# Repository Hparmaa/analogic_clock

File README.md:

# Cronômetro Digital TTL/CMOS

Projeto de um cronômetro digital utilizando circuitos TTL/CMOS, displays de 7 segmentos e alimentação diretamente da rede elétrica da CEMIG.

## Licença

Este projeto é licenciado sob a CERN-OHL-S v2.

## Recursos do projeto

- Contagem de minutos e segundos
- Clock derivado da rede elétrica de 60 Hz
- Displays de 7 segmentos
- Circuitos TTL/CMOS
- Projeto desenvolvido no KiCad
## 
1.	OBJETIVO
   
Projetar e implementar um cronômetro digital capaz de contar os segundos e minutos. O dispositivo deverá ser alimentado exclusivamente a partir da rede elétrica da CEMIG. O cronômetro deverá possuir dois botões, sendo um para iniciar e parar a contagem do tempo (start/stop) e outro para zerar a contagem (reset). Os segundos e minutos serão mostrados em quatro displays de sete segmentos, sendo dois para os segundos (dezena e unidade) e dois para os minutos (dezena e unidade).

## 
2.	DESENVOLVIMENTO
   
O sistema foi dividido em três subsistemas distintos e interligados, sendo eles : 

•	Circuito para a alimentação e geração de clock;

•	Circuito lógico de contagem;

•	Circuito para mostrar a contagem.

A seguir será apresentado o desenvolvimento de cada um destes subsistemas. Todos os diagramas foram montados no software KiCAD.

2.1.	Circuito para a Alimentação e Geração de Clock

De acordo com o meu objetivo ao realizar esse projeto, o cronômetro digital deverá ser alimentado exclusivamente a partir da rede elétrica da CEMIG, a qual possui uma tensão senoidal com tensão eficaz de 127 V e 60 Hz. Considerando que os circuitos integrados a serem utilizados serão do tipo TTL ou CMOS, alimentados em 5 V, tensão contínua, será necessário converter a tensão alternada de 127 VAC em 5 VCC. Por isso, utilizei um retificador de onda completa com um regulador linear de tensão.
O circuito lógico de contagem requer um sinal de clock com frequência fixa e níveis adequados de tensão para uma contagem precisa. Sei que a rede elétrica da CEMIG provê uma senoide com frequência de 60 Hz. Portanto, optei por condicionar a senoide fornecida pela CEMIG para gerar um clock com os mesmos 60 Hz, o qual será posteriormente utilizado no circuito lógico de contagem.
A Figura 1 apresenta o circuito desenvolvido para a alimentação e geração de clock.

Figura 1 – Circuito para alimentação e geração de clock.

Para um adequado funcionamento do circuito de geração do clock e circuito de alimentação, será utilizado um transformador de três enrolamentos de 127 V/7,5 V/7,5 V. Entretanto, considerando que não foi encontrado este tipo de transformador no comércio local, na montagem, foram utilizados dois transformadores distintos, um de 1 A e outro de 0,5 A.

Os componentes para o circuito de geração de clock foram escolhidos conforme explicado a seguir:

Tensão de saída do enrolamento do transformador de 7,5 V, 500 mA.

D9: diodo zenner. Foi escolhido um diodo zenner de 5,1 Volts quando é reversamente polarizado. Quando diretamente polarizado sua tensão é de 1,5 V. Vou considerar que ali vai passar metade da corrente máxima(200mA) suportada por ele, ou seja, projetei o resistor R35 para 100mA.

R35: utilizado para limitar a corrente do diodo zenner. Considerando a corrente máxima no zenner em função de sua potência máxima (de acordo com o datasheet) e a tensão de pico da senoide na saída do transformador (pior caso da tensão), quando o zenner estiver diretamente polarizado, tem-se:
R35=(10,6-1,5)/0,1
R35=91 Ω

Para este valor de resistência, haverá uma potência dissipada de:
P=(7,5-1,5)*0,1
P=0,6 W
Comercialmente foi escolhido um resistor de 100 Ω e 1 W.

D12: diodo de germânio. Escolhi um diodo de germânio pois, quando diretamente polarizado, possui uma tensão direta de  0,3 V, e este valor está dentro da faixa de valores permitidos pelo Schimdt trigger. A corrente máxima de diodos comuns como o 1N34A tem como corrente máxima 50 mA, valor que eu utilizei para calcular o valor da resistência R36.

R36: utilizado para limitar a corrente no diodo de germânio. 

R36=(1,5-0,3)/0,05
R36=24 Ω
Para este valor de resistência, haverá uma potência dissipada de:
P=(1,5-0,3)*0,05
P=0,06 W
Comercialmente foi escolhido um resistor de 24 Ω e 1/4 W.

CI U44: Schimdt trigger. Utilizado para o condicionamento final da senoide ceifada. Escolhi um Schimdt trigger alimentado com 5 Volts e cuja tensão de entrada varie de -0,5 até Vcc + 0,5. Segundo o datasheet, ele funciona, para 4,5 V de alimentação, com uma mudança para nível logico alto de 3,15 V e com a mudança para nível lógico baixo de 2,3 V. Escolhi o 74HC14A

Dessa forma, após o condicionamento da senoide entregue pela CEMIG, teremos um CLK1 de 60 Hz, com as tensões adequadas para os níveis lógicos 1 e 0, com relação ao referencial GND.

Os componentes para o circuito de alimentação foram escolhidos conforme explicado a seguir:

Tensão de saída do enrolamento do transformador de 7,5 V (valor eficaz), corrente de 1 A.

D7,D8, D10 e D11: Ponte retificadora em onda completa. Foram definidos os diodos 1N4007, amplamente utilizados neste tipo de circuito. Estes diodos suportam, facilmente, a corrente máxima do regulador de tensão. Foi considerada uma corrente de carga máxima de 1 A.
  
U43: Regulador linear de tensão. Foi escolhido o LM7805, o qual possui uma corrente máxima de 1 A e tensão de saída de 5 V.
  
C4: capacitor de saída da ponte retificadora completa. Utilizado para limitar a tensão de ripple da fonte. O LM7805 requer uma tensão mínima de 7 V para que eu tenha 5V na saída, logo, o meu ripple tem que ser de (10,6-7) = 3,6 V. Assim, minha capacitância é de: 

  C=I/(Vripple*f)
  
  C=1/(3,6*120)

  C=2,31 mF

Esse capacitor deverá ser eletrolítico e sua tensão máxima será de (10,6-1,4) =  9,2 V. 
Considerando valores comerciais, foi escolhido um capacitor eletrolítico de 2200 microF, 25 V.

C5: capacitor de disco de cerâmica de 0,22 microF, indicado no datasheet do LM7805.
  C6: capacitor de disco de cerâmica de 0,1 microF, indicado no datasheet do LM7805.

Desta forma, na saída do circuito de alimentação teremos uma tensão contínua de 5 V, com relação ao referencial GND.

Optou-se por implementar o circuito para alimentação e geração do clock em uma placa de circuito impressa. A Figura 2 apresenta o diagrama de roteamento da placa desenvolvida, vista pelo lado dos componentes. Ressalta-se que as ilhas dos conectores de entrada (transformador) e saída (GND, + 5 V e CLK1) não condizem com a realidade. Da mesma forma, a largura das trilhas também não condiz com a realidade implementada. A numeração dos componentes não possui relação direta com a numeração apresentada na Figura 1.

Figura 2: Diagrama de roteamento da placa do circuito para alimentação e geração do clock.

2.2.	Circuito Lógico de Contagem
O circuito lógico de contagem é o circuito responsável pela lógica de contagem do cronômetro. Esse circuito receberá o sinal de CLK1 e a tensão de 5 VDC da placa de alimentação e geração clock.
A Figura 3 apresenta o circuito lógico de contagem.

Figura 3: Diagrama do circuito lógico de contagem.

Conforme dito, o circuito lógico de contagem recebe o sinal de clock CLK1, que possui frequência de 60 Hz. Considerando que a menor medida de tempo a ser contada são os segundos, será necessário dividir essa frequência por 60. Para isso, foi projetado um contador síncrono, módulo-60, que conte de 0 a 59, ou seja, ao chegar em 60, ou 111100 em binário, ele resete. Dessa forma, na saída desse divisor teremos um clock de 1 Hz. Esse circuito possui, ainda, as chaves de start/stop, sendo ela uma chave de duas posições e a chave de reset, do tipo push bottom.

A saída do divisor módulo-60 (com frequencia de 1 Hz) alimentará um circuito com contadores de década utilizado para a contagem dos segundos e minutos.

Os componentes para o circuito de lógica de contagem foram escolhidos conforme explicado a seguir:

  •	CIs U27, U28 e U28. Foram utilizados seis flip-flops do tipo JK, configurados como flip-flop tipo T, para a implementação do divisor módulo-60. Foi escolhido o CI 4027.

  •	CI U38: para a implementação do divisor módulo-60 foi necessário utilizar uma AND de quatro entradas, utilizada para zerar os flip-flops tipo T quando a contagem chega em 111100. Foi escolhido o CI 7421.
  
  •	SW4: chave de duas posições, on/off. Utilizada para implementar o sistema de start/stop do cronômetro. Essa chave habilita ou desabilita a saída do clock do divisor módulo-60 para o circuito contador dos segundos e minutos.
  
  •	CI U35A: porta AND de duas entradas, utilizado para implementar a lógica de habilitação/desabilitação do sinal de clock de saída do divisor módulo-60.
  
  •	CIs U29, U32, U39 e U40: Decidi utilizar contadores de década (contagem BCD) para a a contagem dos segundos e minutos de forma assíncrona. 
     
Os CIs U29 e U32 são utilizados para a contagem dos segundos (contagem de 0 a 59), utilizando o sinal de clock de saída do divisor de módulo-60. O CI U29 é utilizado para a contagem das unidades de segundo e o CI U32 para a contagem das dezenas de segundos, utilizando a saída do CI U29 como sinal de clock, após a divisão por 10. Os dois contadores são zerados quando U32 atinge o número 6, 0110 em binário, o que equivale a chegar ao número 60 nos dois contadores (conta de 0 a 59 segundos).
 
  Os CIs U39 e U40 são utilizados para a contagem dos minutos (contagem de 0 a 59), utilizando como clock a saída do CI U32. Os dois contadores são zerados quando U40 atinge o número 6 (0110 em binário), o que equivale a chegar ao número 60 nos dois contadores (conta de 0 a 59 minutos).

  •	SW3: chave NA do tipo push bottom. Utilizada para implementar o sistema de reset do cronômetro. Ao ser pressionada os contadores BCD (CIs U29, U32, U39 e U40, responsáveis por contar os segundos e minutos) são resetados.

  •	CI U36: porta OR de duas entradas. Utilizado para implementar a lógica do botão de reset.
  
  •	R33 e R34: resistores utilizados em série com as chaves SW3 e SW4 para a implementação das lógicas de start/stop e reset. Foram utilizados resistores de 10 kΩ, valor suficiente para limitar a corrente quando as chaves forem acionadas sem prejudicar o valor dos níveis digitais aplicados às entradas das portas lógicas.
  
  •	J1, J2, J3 e J4: conectores de 4 pinos para disponibilizar os quatro bits da saída dos contadores de década (contagem BCD).

A saída do circuito lógico de contagem são quatro conjuntos de quatro bits (contagem BCD), responsáveis pela contagem das unidades de segundos, dezenas de segundos, unidades de minutos e dezenas de minutos. Esses sinais são disponibilizados nos conectores J1 a J4.

  Optou-se por implementar o circuito lógico de contagem em um protoboard, devido a complexidade deste circuito.

2.3.	Circuito para Mostrar a Contagem

O circuito para mostrar a contagem é o circuito responsável por mostrar, ao usuário, a contagem do cronômetro.  Esse circuito receberá a tensão de 5 VDC da placa de alimentação e geração clock e os quatro conjuntos de quatro bits (contagem BCD) do circuito lógico de contagem.

  O valor da contagem dos segundos e minutos será apresentado em displays de sete segmentos, totalizando quatro display, dois para os segundos (unidades e dezenas) e dois para os minutos (unidades e dezenas). Para a implementação foram utilizados conversores BCD para 7 segmentos.
  
A Figura 4 apresenta o diagrama do circuito para mostrar o valor da contagem.

Figura 4: Diagrama do circuito para mostrar a contagem.

Os componentes do circuito para mostrar a contagem foram escolhidos conforme explicado a seguir:

J5, J6, J7 e J8: conectores de 4 pinos para receber os quatros bits da contagem da unidade dos segundos, dezena dos segundos, unidade dos minutos e dezena dos minutos.
  
U30, U33, U41 e U45: conversores de BCD para 7 segmentos. Foram utilizados o CI 4511.
  
R37 a R64 (28 resistores): resistores utilizados para limitar a corrente fornecida pelos conversores de BCD para 7 segmentos, considerando a corrente necessária para o adequado funcionamento dos displays de 7 segmentos.
  
Para os leds dos displays acenderem em intensidade média, o datasheet e indica que é necessário 10 mA, logo, usarei 12mA. O datasheet informa, também, que a tensão direta dos leds é de 2 V. Considerando a saída em 5 V do conversor BCD para 7 segmentos, temos:

R=(5-2)/0,012

R=250 Ω

Para esse valor de resistência, a potência será de:

P=3*0,012

P=0,036 W

Será utilizado o valor comercial de R = 250 Ω e ¼ W.

U31, U34, U37 e U47: displays de 7 segmentos de alto brilho, na cor vermelha. Foram utilizados displays de catodo comum, tendo sido utilizado o modelo 5161AS, disponível no comércio local.

SW5: chave NA do tipo push bottom utilizada para implementar o teste dos displays.

R65: resistor utilizado em série com a chave SW5 para a implementação das lógicas teste dos displays. Foi utilizado um resistor de 1,0 kΩ., valor suficiente para limitar a corrente quando a chave for acionada sem prejudicar o valor dos níveis digitais aplicados às entradas dos conversores BCD para 7 segmentos.

Optou-se por implementar o circuito para mostrar a contagem em uma placa de circuito impressa. A Figura 5 apresenta o diagrama de roteamento da placa desenvolvida, vista pelo lado dos componentes. Ressalta-se que a largura das trilhas não condiz com a realidade implementada. A numeração dos componentes não possui relação direta com a numeração apresentada na Figura 4.

Figura 5 - Diagrama de roteamento da placa do circuito para mostrar a contagem.

## 
3.	CONCLUSÃO

Neste trabalho foi projetado um cronômetro digital capaz de marcar os segundos e minutos a partir do comando do usuário, dados por chaves. O cronômetro digital é alimentado a partir da rede elétrica da CEMIG, sendo que o sinal de clock é gerado a partir do condicionamento da senoide de tensão da alimentação, o que garante estabilidade na contagem.

O valor da contagem é apresentado em quatro displays de sete segmentos na cor vermelha e alto brilho.

O projeto foi segmentado em três subsistemas, o primeiro dedicado à geração de tensão contínua de 5 V, com relação ao GND, a ser utilizada em todo o projeto e à geração do sinal de clock de 60 Hz a partir da própria senoide da tensão de alimentação. O segundo dedicado à contagem propriamente dita do cronômetro. O terceiro dedicado a apresentar o valor da contagem ao usuário.

O primeiro e terceiro subsistemas foram implementados em placas de circuito impresso. O segundo sistema foi implementado em um protoboard.

Infelizmente, devido a complexidade do projeto pretendido e à falta de tempos disponível, não foi possível concluir satisfatoriamente o segundo sistema, não sendo possível, portanto, testar todo o sistema proposto. Entende-se, entretanto, que após a finalização do segundo sistema o projeto proposto funcionará a contento.

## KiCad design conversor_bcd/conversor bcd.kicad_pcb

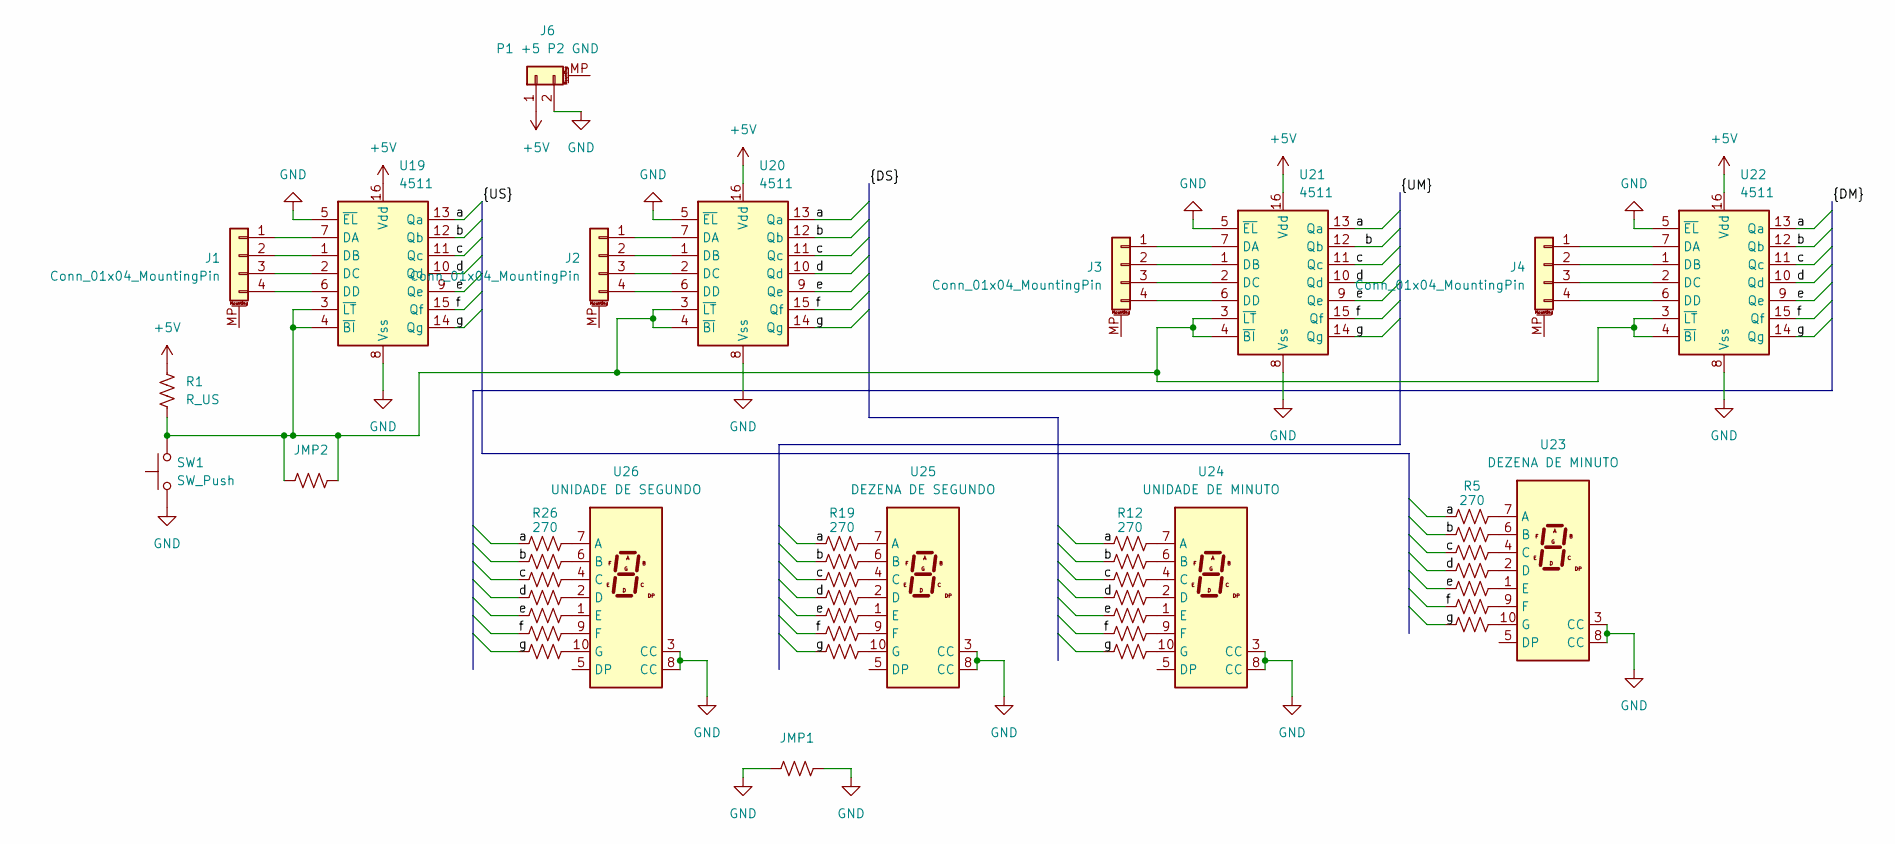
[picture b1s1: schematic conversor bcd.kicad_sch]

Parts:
J1, J2, J3, J4: Conn_01x04_MountingPin; FanPinHeader_1x04_P2.54mm_Vertical
J6: P1 +5 P2 GND; FanPinHeader_1x03_P2.54mm_Vertical
JMP1, JMP2: 1; R_Axial_DIN0411_L9.9mm_D3.6mm_P7.62mm_Vertical
R1: R_US; R_Axial_DIN0411_L9.9mm_D3.6mm_P15.24mm_Horizontal
R5, R6, R7, R8, R9, R10, R11, R12, R13, R14, R15, R16, R17, R18, R19, R20, R21, R22, R23, R24, R25, R26, R27, R28, R29, R30, R31, R32: 270; R_Axial_DIN0411_L9.9mm_D3.6mm_P15.24mm_Horizontal
SW1: SW_Push; SW_PUSH_1P1T_6x3.5mm_H4.3_APEM_MJTP1243
U19, U20, U21, U22: 4511; DIP-16_W7.62mm_Socket
U23: DEZENA DE MINUTO; D1X8K
U24: UNIDADE DE MINUTO; D1X8K
U25: DEZENA DE SEGUNDO; D1X8K
U26: UNIDADE DE SEGUNDO; D1X8K

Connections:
+5V: J6.1, R1.1, U19.16 (Vdd), U20.16 (Vdd), U21.16 (Vdd), U22.16 (Vdd)
/a: R5.1, R12.1, R19.1, R26.1, U19.13 (Qa), U20.13 (Qa), U21.13 (Qa), U22.13 (Qa)
/b: R6.1, R13.1, R20.1, R27.1, U19.12 (Qb), U20.12 (Qb), U21.12 (Qb), U22.12 (Qb)
/c: R7.1, R14.1, R21.1, R28.1, U19.11 (Qc), U20.11 (Qc), U21.11 (Qc), U22.11 (Qc)
/d: R8.1, R15.1, R22.1, R29.1, U19.10 (Qd), U20.10 (Qd), U21.10 (Qd), U22.10 (Qd)
/e: R9.1, R16.1, R23.1, R30.1, U19.9 (Qe), U20.9 (Qe), U21.9 (Qe), U22.9 (Qe)
/f: R10.1, R17.1, R24.1, R31.1, U19.15 (Qf), U20.15 (Qf), U21.15 (Qf), U22.15 (Qf)
/g: R11.1, R18.1, R25.1, R32.1, U19.14 (Qg), U20.14 (Qg), U21.14 (Qg), U22.14 (Qg)
GND: J6.2, JMP1.1, JMP1.2, SW1.1, U19.5 (~EL), U19.8 (Vss), U20.5 (~EL), U20.8 (Vss), U21.5 (~EL), U21.8 (Vss), U22.5 (~EL), U22.8 (Vss), U23.3 (CC), U23.8 (CC), U24.3 (CC), U24.8 (CC), U25.3 (CC), U25.8 (CC), U26.3 (CC), U26.8 (CC)
unnamed: J1.1, U19.7 (DA)
unnamed: J1.2, U19.1 (DB)
unnamed: J1.3, U19.2 (DC)
unnamed: J1.4, U19.6 (DD)
unnamed: J2.1, U20.7 (DA)
unnamed: J2.2, U20.1 (DB)
unnamed: J2.3, U20.2 (DC)
unnamed: J2.4, U20.6 (DD)
unnamed: J3.1, U21.7 (DA)
unnamed: J3.2, U21.1 (DB)
unnamed: J3.3, U21.2 (DC)
unnamed: J3.4, U21.6 (DD)
unnamed: J4.1, U22.7 (DA)
unnamed: J4.2, U22.1 (DB)
unnamed: J4.3, U22.2 (DC)
unnamed: J4.4, U22.6 (DD)
unnamed: JMP2.1, JMP2.2, R1.2, SW1.2, U19.3 (~LT), U19.4 (~BI), U20.3 (~LT), U20.4 (~BI), U21.3 (~LT), U21.4 (~BI), U22.3 (~LT), U22.4 (~BI)
unnamed: R5.2, U23.7 (A)
unnamed: R6.2, U23.6 (B)
unnamed: R7.2, U23.4 (C)
unnamed: R8.2, U23.2 (D)
unnamed: R9.2, U23.1 (E)
unnamed: R10.2, U23.9 (F)
unnamed: R11.2, U23.10 (G)
unnamed: R12.2, U24.7 (A)
unnamed: R13.2, U24.6 (B)
unnamed: R14.2, U24.4 (C)
unnamed: R15.2, U24.2 (D)
unnamed: R16.2, U24.1 (E)
unnamed: R17.2, U24.9 (F)
unnamed: R18.2, U24.10 (G)
unnamed: R19.2, U25.7 (A)
unnamed: R20.2, U25.6 (B)
unnamed: R21.2, U25.4 (C)
unnamed: R22.2, U25.2 (D)
unnamed: R23.2, U25.1 (E)
unnamed: R24.2, U25.9 (F)
unnamed: R25.2, U25.10 (G)
unnamed: R26.2, U26.7 (A)
unnamed: R27.2, U26.6 (B)
unnamed: R28.2, U26.4 (C)
unnamed: R29.2, U26.2 (D)
unnamed: R30.2, U26.1 (E)
unnamed: R31.2, U26.9 (F)
unnamed: R32.2, U26.10 (G)

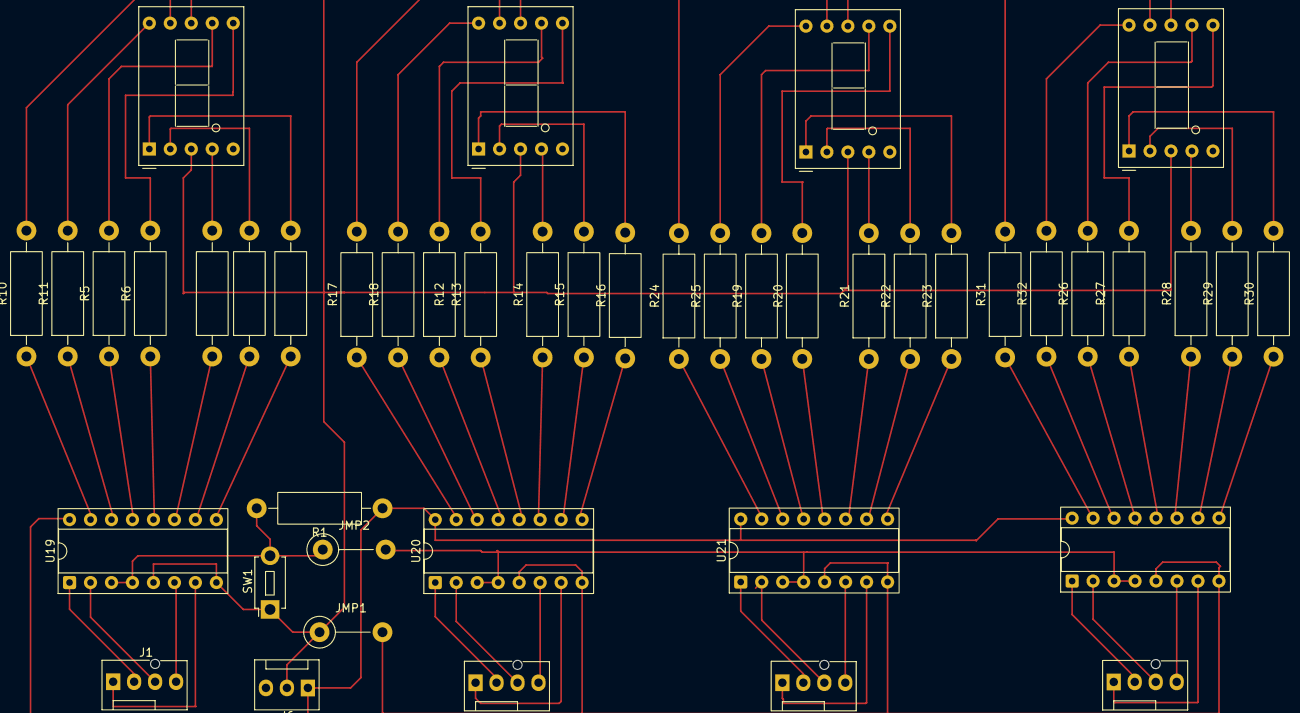
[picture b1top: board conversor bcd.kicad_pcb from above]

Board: 2 copper layers, 45 parts (0 on the bottom side), 54 nets.

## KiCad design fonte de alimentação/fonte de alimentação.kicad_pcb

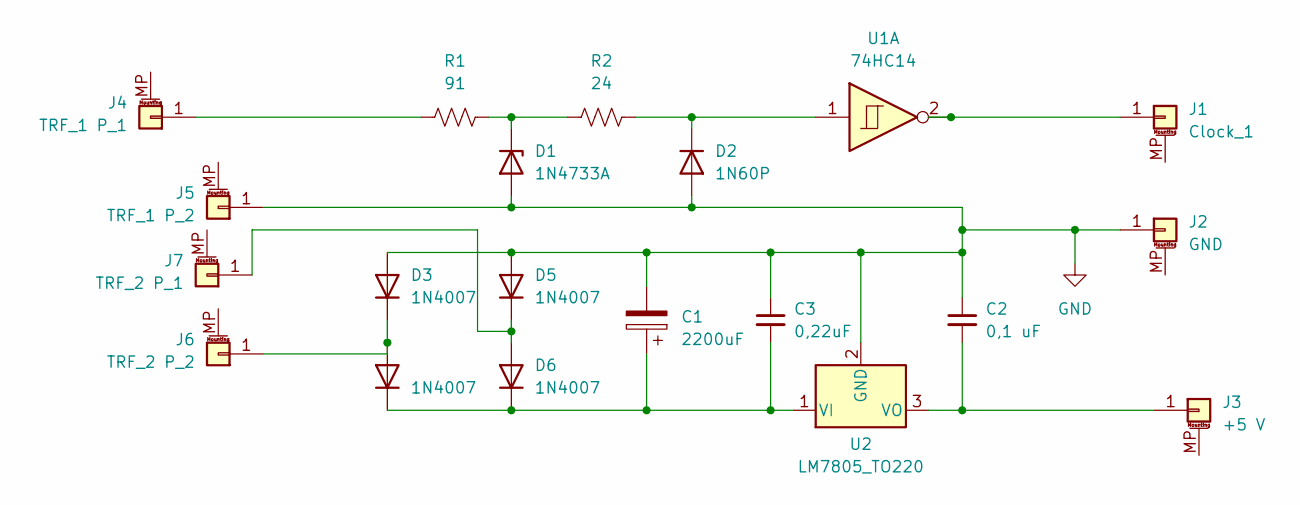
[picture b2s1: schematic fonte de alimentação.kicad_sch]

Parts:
C1: 2200uF; CP_Radial_D13.0mm_P5.00mm
C2: 0,1 uF; C_Disc_D14.5mm_W5.0mm_P10.00mm
C3: 0,22uF; C_Disc_D7.5mm_W5.0mm_P5.00mm
D1: 1N4733A; D_DO-41_SOD81_P10.16mm_Horizontal
D2: 1N60P; D_DO-41_SOD81_P10.16mm_Horizontal
D3, D4, D5, D6: 1N4007; D_DO-41_SOD81_P10.16mm_Horizontal
J1: Clock_1; Banana_Jack_1Pin
J2: GND; Banana_Jack_1Pin
J3: +5 V; Banana_Jack_1Pin
J4: TRF_1 P_1; Banana_Jack_1Pin
J5: TRF_1 P_2; Banana_Jack_1Pin
J6: TRF_2 P_2; Banana_Jack_1Pin
J7: TRF_2 P_1; Banana_Jack_1Pin
R1: 91; R_Axial_DIN0516_L15.5mm_D5.0mm_P20.32mm_Horizontal
R2: 24; R_Axial_DIN0414_L11.9mm_D4.5mm_P15.24mm_Horizontal
U1: 74HC14; CERDIP-14_W7.62mm_SideBrazed
U2: LM7805_TO220; TO-220-3_Vertical

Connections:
GND: C1.2, C2.1, C3.1, D1.2 (A), D2.2 (A), D3.2 (A), D5.2 (A), J2.1, J5.1, U2.2 (GND)
unnamed: D1.1 (K), R1.2, R2.1
unnamed: D2.1 (K), R2.2, U1.1
unnamed: D3.1 (K), D4.2 (A), J6.1
unnamed: C1.1, C3.2, D4.1 (K), D6.1 (K), U2.1 (VI)
unnamed: D5.1 (K), D6.2 (A), J7.1
unnamed: J1.1, U1.2
unnamed: C2.2, J3.1, U2.3 (VO)
unnamed: J4.1, R1.1

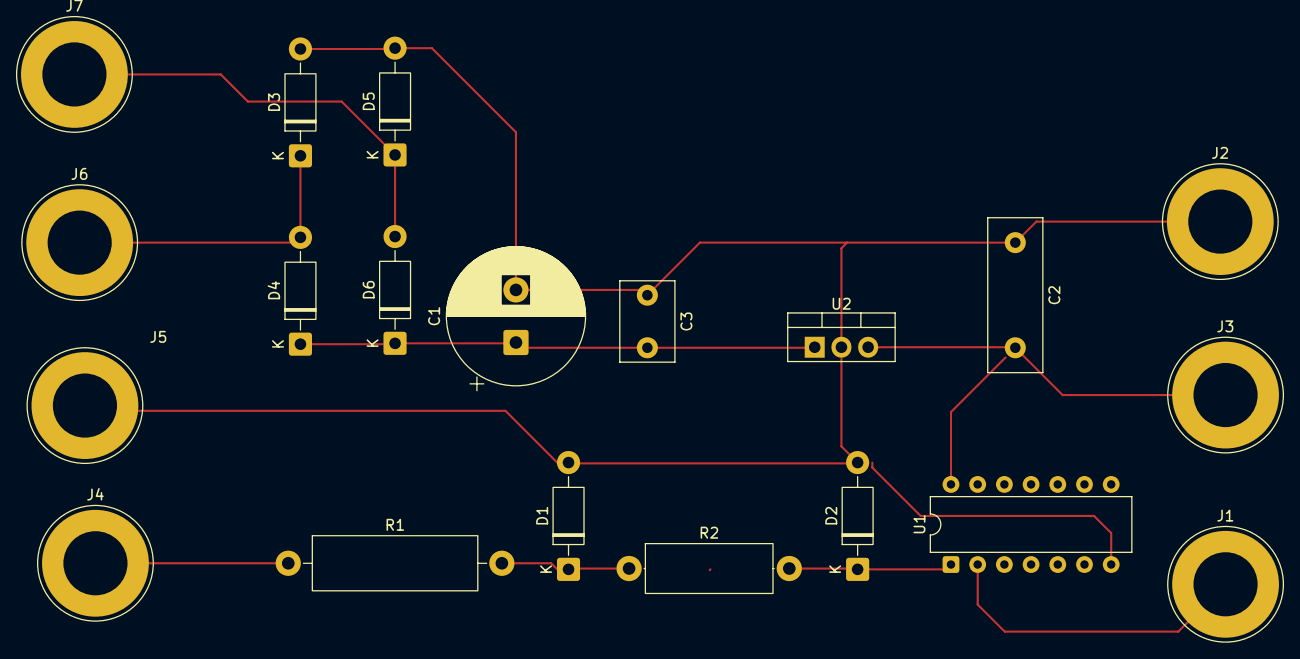
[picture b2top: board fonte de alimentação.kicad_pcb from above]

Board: 2 copper layers, 20 parts (0 on the bottom side), 9 nets.

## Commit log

2026-06-21 Create LICENSE
